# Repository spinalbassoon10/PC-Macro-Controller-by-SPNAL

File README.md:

# PC-Macro-Controller-by-SPNAL

# Screenshots
PCB in Case:

Schematic:

PCB:

Case:

# BOM:
- Seeed XIAO RP2040 x1 <br>
- Through-hole 1N4148 Diodes x9 <br>
- EC11 Rotary encoder x1 <br>
- Blank DSA keycaps (White) <br>
- SK6812 MINI-E LEDs x1 <br>
- MX-Style switches x9 <br>
- M3x16mm screws x4 <br>
- Case <br>

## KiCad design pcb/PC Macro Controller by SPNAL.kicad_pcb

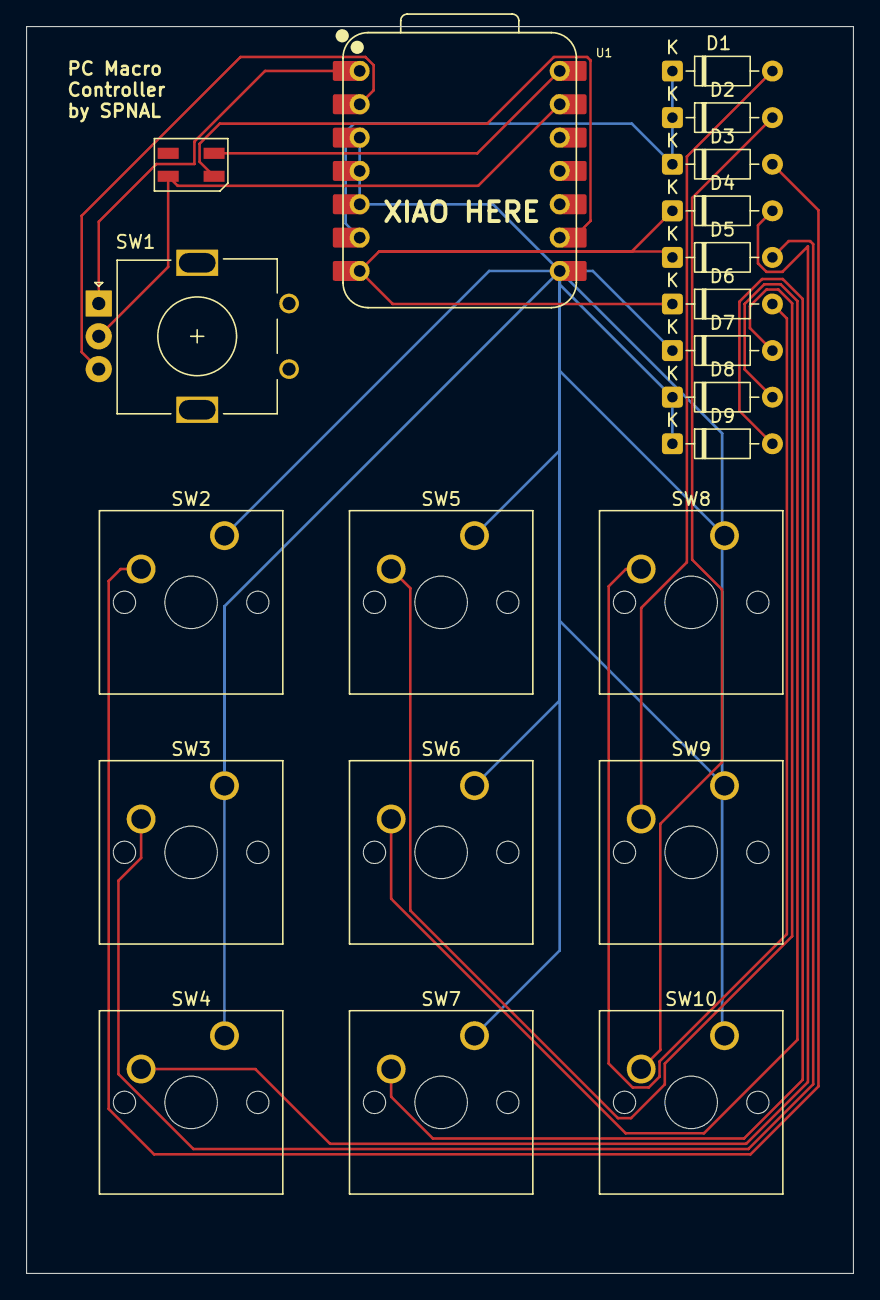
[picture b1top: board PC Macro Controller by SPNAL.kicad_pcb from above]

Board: 2 copper layers, 63.0 x 95.0 mm, 21 parts (0 on the bottom side), 17 nets.

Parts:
D1, D2, D3, D4, D5, D6, D7, D8, D9: D; D_DO-35_SOD27_P7.62mm_Horizontal
D10: SK6812MINI; LED_SK6812MINI_PLCC4_3.5x3.5mm_P1.75mm
SW1: RotaryEncoder_Switch; RotaryEncoder_Alps_EC11E_Vertical_H20mm
SW2, SW3, SW4, SW5, SW6, SW7, SW8, SW9, SW10: SW_Push; SW_Cherry_MX_1.00u_PCB
U1: XIAO-RP2040-DIP

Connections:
+5V: D10.4 (VDD), U1.14 (VBUS)
GND: D10.2 (VSS), SW1.C, U1.13 (GND)
unnamed: D1.2 (A), SW9.2
unnamed: D2.2 (A), SW10.2
unnamed: D3.2 (A), SW2.2
unnamed: D4.2 (A), SW4.2
unnamed: D5.2 (A), SW3.2
unnamed: D6.2 (A), SW8.2
unnamed: D7.2 (A), SW5.2
unnamed: D8.2 (A), SW6.2
unnamed: D9.2 (A), SW7.2
unnamed: D10.3 (DIN), U1.9 (GPIO2/SCK)
unnamed: SW1.A, U1.1 (GPIO26/ADC0/A0)
unnamed: SW1.B, U1.2 (GPIO27/ADC1/A1)
col1: D7.1 (K), D8.1 (K), D9.1 (K), SW2.1, SW3.1, SW4.1, SW5.1, SW6.1, SW7.1, SW8.1, SW9.1, SW10.1, U1.3 (GPIO28/ADC2/A2), U1.4 (GPIO29/ADC3/A3), U1.5 (GPIO6/SDA), U1.8 (GPIO1/RX)
row1: D1.1 (K), D2.1 (K), D3.1 (K), U1.6 (GPIO7/SCL)
row2: D4.1 (K), D5.1 (K), D6.1 (K), U1.7 (GPIO0/TX)

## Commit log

2025-12-04 Create temp
2025-12-04 Rename Controller Assembly.png to Controller_Assembly.png
